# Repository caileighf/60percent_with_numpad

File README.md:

# 60percent_with_numpad
60 percent mechanical keyboard with support for a numpad to be connected magnetically

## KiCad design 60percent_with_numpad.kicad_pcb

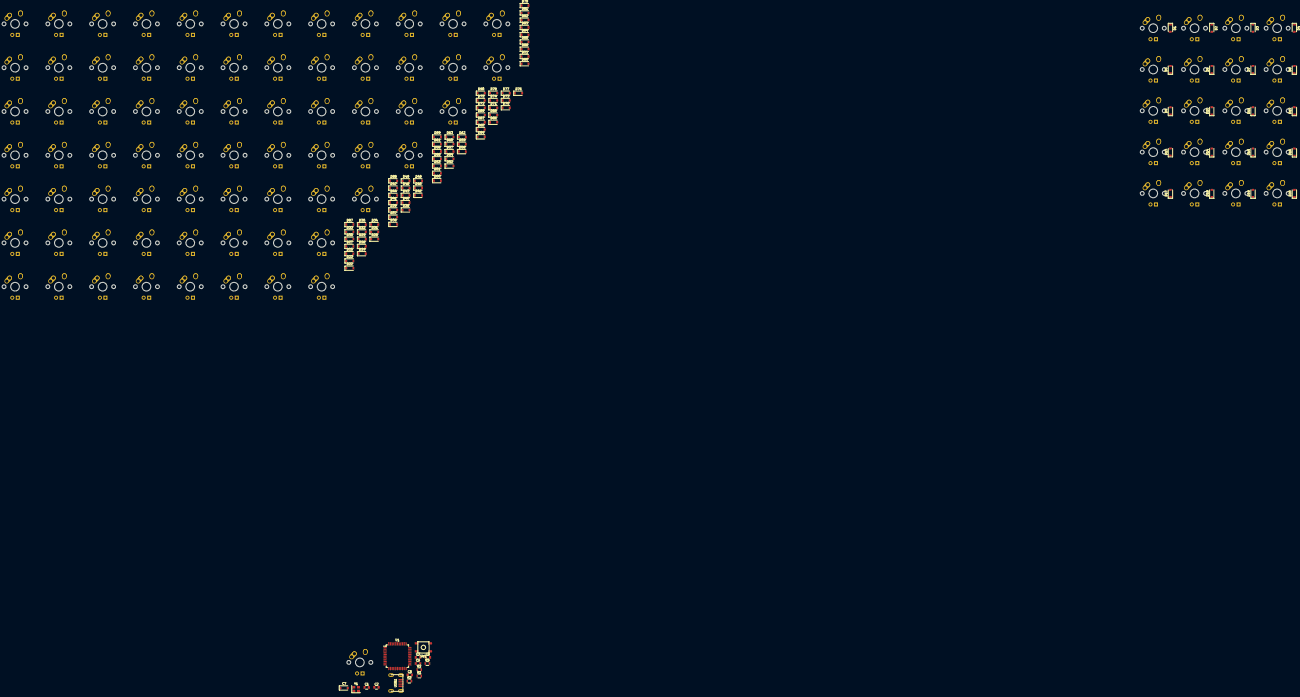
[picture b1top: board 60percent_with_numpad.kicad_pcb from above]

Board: 2 copper layers, 196 parts (0 on the bottom side), 125 nets, no tracks yet.

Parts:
C1: 1uF; C_0805
C2, C3, C4: 0.1uF; C_0805
C5: 10uF; C_0805
C6: 22pF; C_0805
C7: 22pF; D_SOD-123
D1, D2, D3, D4, D5, D6, D7, D8, D9, D10, D11, D12, D13, D14, D15, D16, D17, D18, D19, D20, D21, D22, D23, D24, D25, D26, D27, D28, D29, D30, D31, D32, D33, D34, D35, D36, D37, D38, D39, D40, D41, D42, D43, D44, D45, D46, D47, D48, D49, D50, D51, D52, D53, D54, D55, D56, D57, D58, D59, D60, D61, D62, D63, D64, D65, D66, D67, D68, D69, D70, D71, D72, D73, D74, D75, D76, D77, D78, D79, D80, D81, D82, D83, D84, D85, D86, D87, D88, D89, D90: SOD-123; D_SOD-123
F1: 500mA; MX-1U
MX1, MX2, MX3, MX4, MX5, MX6, MX7, MX8, MX9, MX10, MX11, MX12, MX13, MX14, MX15, MX16, MX17, MX18, MX19, MX20, MX21, MX22, MX23, MX24, MX25, MX26, MX27, MX28, MX29, MX30, MX31, MX32, MX33, MX34, MX35, MX36, MX37, MX38, MX39, MX40, MX41, MX42, MX43, MX44, MX45, MX46, MX47, MX48, MX49, MX50, MX51, MX52, MX53, MX54, MX55, MX56, MX57, MX58, MX59, MX60, MX61, MX62, MX63, MX64, MX65, MX66, MX67, MX68, MX69, MX70, MX71, MX72, MX73, MX74, MX75, MX76, MX77, MX78, MX79, MX80, MX81, MX82, MX83, MX84, MX85, MX86, MX87, MX88, MX89, MX90: MX-1U
R1, R2: 10k; R_0805
R3, R4: 22; R_0805
SW1: SW_Push; SKQG-1155865
U1: ATmega32U4-AU; TQFP-44_10x10mm_Pitch0.8mm
USB1: Molex-0548190589
Y1: 16MHz; Crystal_SMD_3225-4pin_3.2x2.5mm

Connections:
+5V: C2.1, C3.1, C4.1, C5.1, F1.1, R2.1, U1.2, U1.7, U1.14, U1.24, U1.34, U1.44
COL0: MX21.1, MX35.1, MX49.1, MX63.1, MX77.1
COL1: MX22.1, MX36.1, MX50.1, MX64.1, MX78.1
COL2: MX23.1, MX37.1, MX51.1, MX65.1, MX79.1
COL3: MX24.1, MX38.1, MX52.1, MX66.1, MX80.1
COL4: MX25.1, MX39.1, MX53.1, MX67.1, MX81.1
COL5: MX26.1, MX40.1, MX54.1, MX68.1, MX82.1
COL6: MX27.1, MX41.1, MX55.1, MX69.1, MX83.1
COL7: MX28.1, MX42.1, MX56.1, MX70.1, MX84.1
COL8: MX29.1, MX43.1, MX57.1, MX71.1, MX85.1
COL10: MX30.1, MX44.1, MX58.1, MX72.1, MX86.1
COL11: MX31.1, MX45.1, MX59.1, MX73.1, MX87.1
COL12: MX32.1, MX46.1, MX60.1, MX74.1, MX88.1
COL13: MX33.1, MX47.1, MX61.1, MX75.1, MX89.1
COL14: MX34.1, MX48.1, MX62.1, MX76.1, MX90.1
COL15: MX1.1, MX5.1, MX9.1, MX13.1, MX17.1
COL16: MX2.1, MX6.1, MX10.1, MX14.1, MX18.1
COL17: MX3.1, MX7.1, MX11.1, MX15.1, MX19.1
COL18: MX4.1, MX8.1, MX12.1, MX16.1, MX20.1
D+: R3.2, USB1.3
D-: R4.2, USB1.4
GND: C1.2, C2.2, C3.2, C4.2, C5.2, C6.2, C7.2, R1.2, SW1.1, U1.5, U1.15, U1.23, U1.35, U1.43, USB1.1, Y1.2, Y1.4
unnamed: C1.1, U1.6
unnamed: C6.1, U1.17, Y1.1
unnamed: C7.1, U1.16, Y1.3
unnamed: D1.2, MX1.2
unnamed: D2.2, MX2.2
unnamed: D3.2, MX3.2
unnamed: D4.2, MX4.2
unnamed: D5.2, MX5.2
unnamed: D6.2, MX6.2
unnamed: D7.2, MX7.2
unnamed: D8.2, MX8.2
unnamed: D9.2, MX9.2
unnamed: D10.2, MX10.2
unnamed: D11.2, MX11.2
unnamed: D12.2, MX12.2
unnamed: D13.2, MX13.2
unnamed: D14.2, MX14.2
unnamed: D15.2, MX15.2
unnamed: D16.2, MX16.2
unnamed: D17.2, MX17.2
unnamed: D18.2, MX18.2
unnamed: D19.2, MX19.2
unnamed: D20.2, MX20.2
unnamed: D21.2, MX21.2
unnamed: D22.2, MX22.2
unnamed: D23.2, MX23.2
unnamed: D24.2, MX24.2
unnamed: D25.2, MX25.2
unnamed: D26.2, MX26.2
unnamed: D27.2, MX27.2
unnamed: D28.2, MX28.2
unnamed: D29.2, MX29.2
unnamed: D30.2, MX30.2
unnamed: D31.2, MX31.2
unnamed: D32.2, MX32.2
unnamed: D33.2, MX33.2
unnamed: D34.2, MX34.2
unnamed: D35.2, MX35.2
unnamed: D36.2, MX36.2
unnamed: D37.2, MX37.2
unnamed: D38.2, MX38.2
unnamed: D39.2, MX39.2
unnamed: D40.2, MX40.2
unnamed: D41.2, MX41.2
unnamed: D42.2, MX42.2
unnamed: D43.2, MX43.2
unnamed: D44.2, MX44.2
unnamed: D45.2, MX45.2
unnamed: D46.2, MX46.2
unnamed: D47.2, MX47.2
unnamed: D48.2, MX48.2
unnamed: D49.2, MX49.2
unnamed: D50.2, MX50.2
unnamed: D51.2, MX51.2
unnamed: D52.2, MX52.2
unnamed: D53.2, MX53.2
unnamed: D54.2, MX54.2
unnamed: D55.2, MX55.2
unnamed: D56.2, MX56.2
unnamed: D57.2, MX57.2
unnamed: D58.2, MX58.2
unnamed: D59.2, MX59.2
unnamed: D60.2, MX60.2
unnamed: D61.2, MX61.2
unnamed: D62.2, MX62.2
unnamed: D63.2, MX63.2
unnamed: D64.2, MX64.2
unnamed: D65.2, MX65.2
unnamed: D66.2, MX66.2
unnamed: D67.2, MX67.2
unnamed: D68.2, MX68.2
unnamed: D69.2, MX69.2
unnamed: D70.2, MX70.2
unnamed: D71.2, MX71.2
unnamed: D72.2, MX72.2
unnamed: D73.2, MX73.2
unnamed: D74.2, MX74.2
unnamed: D75.2, MX75.2
unnamed: D76.2, MX76.2
unnamed: D77.2, MX77.2
unnamed: D78.2, MX78.2
unnamed: D79.2, MX79.2
unnamed: D80.2, MX80.2
unnamed: D81.2, MX81.2
unnamed: D82.2, MX82.2
unnamed: D83.2, MX83.2
unnamed: D84.2, MX84.2
unnamed: D85.2, MX85.2
unnamed: D86.2, MX86.2
unnamed: D87.2, MX87.2
unnamed: D88.2, MX88.2
unnamed: D89.2, MX89.2
unnamed: D90.2, MX90.2
unnamed: R1.1, U1.33
unnamed: R2.2, SW1.2, U1.13
unnamed: R3.1, U1.4
unnamed: R4.1, U1.3
ROW0: D1.1, D2.1, D3.1, D4.1, D21.1, D22.1, D23.1, D24.1, D25.1, D26.1, D27.1, D28.1, D29.1, D30.1, D31.1, D32.1, D33.1, D34.1
ROW1: D5.1, D6.1, D7.1, D8.1, D35.1, D36.1, D37.1, D38.1, D39.1, D40.1, D41.1, D42.1, D43.1, D44.1, D45.1, D46.1, D47.1, D48.1
ROW2: D9.1, D10.1, D11.1, D12.1, D49.1, D50.1, D51.1, D52.1, D53.1, D54.1, D55.1, D56.1, D57.1, D58.1, D59.1, D60.1, D61.1, D62.1
ROW3: D13.1, D14.1, D15.1, D16.1, D63.1, D64.1, D65.1, D66.1, D67.1, D68.1, D69.1, D70.1, D71.1, D72.1, D73.1, D74.1, D75.1, D76.1
ROW4: D17.1, D18.1, D19.1, D20.1, D77.1, D78.1, D79.1, D80.1, D81.1, D82.1, D83.1, D84.1, D85.1, D86.1, D87.1, D88.1, D89.1, D90.1
VCC: F1.2, USB1.5

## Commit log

2019-05-30 adding kicad files and submodules
2019-05-30 progress on schematic
2019-06-03 split into h-sheets
